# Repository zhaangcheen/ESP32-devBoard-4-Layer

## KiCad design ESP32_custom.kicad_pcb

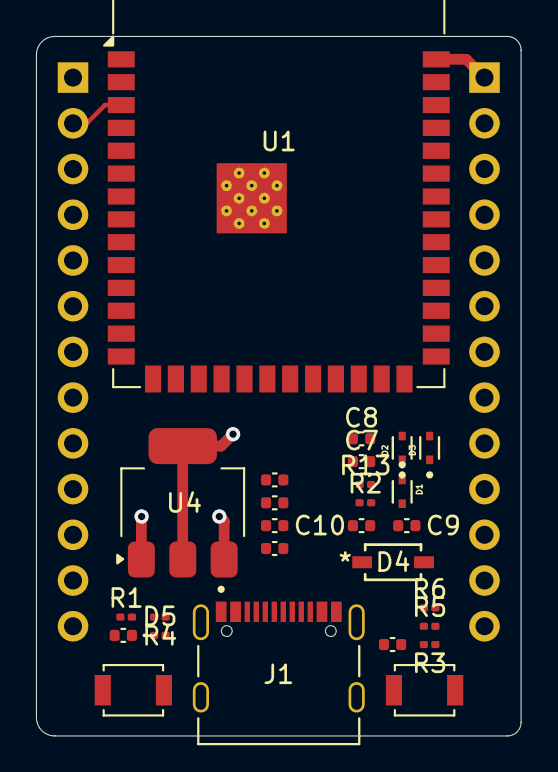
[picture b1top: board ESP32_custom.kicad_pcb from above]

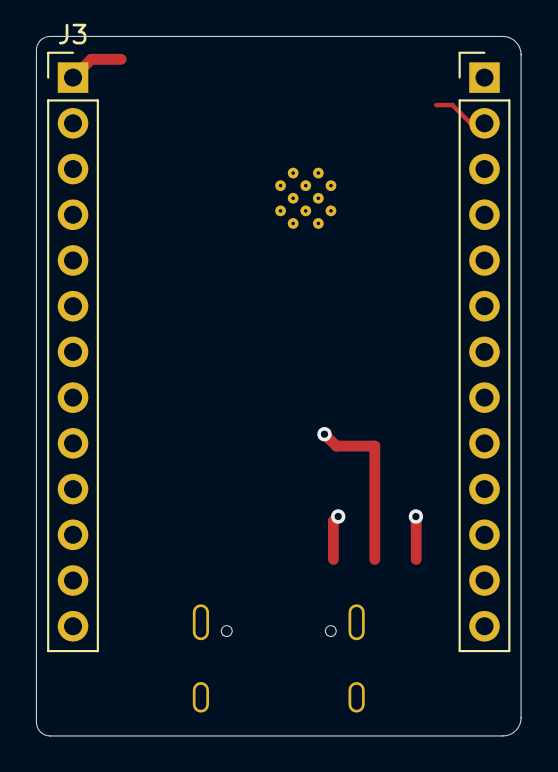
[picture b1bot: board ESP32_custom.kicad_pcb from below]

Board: 4 copper layers, 26.9 x 38.9 mm, 29 parts (2 on the bottom side), 14 nets.

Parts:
C1, C3, C5, C6, C7: 0u1F; C_0402_1005Metric
C2, C4, C8, C9: 10uF; C_0402_1005Metric
C10: 1uF; C_0402_1005Metric
D1, D2, D3: LESD5D5.0CT1G; TVS_LESD5D5.0CT1G
D4: 1N5819HW-7-F; 1N5819HW-7-F_DIO
D5: LED; LED_0201_0603Metric
J1: TYPE-C-31-M-12; HRO_TYPE-C-31-M-12
J2, J3: Conn_01x13_Pin; PinHeader_1x13_P2.54mm_Vertical
R1: 5.1K; R_0201_0603Metric
R2, R3, R13: 10K; R_0201_0603Metric
R4: 10k; R_0201_0603Metric
R5, R6: 5K1; R_0201_0603Metric
SW1, SW2: SW_Push; SW_SPST_B3U-1000P
U1: ESP32-S3-WROOM-1
U4: AMS1117-3.3; SOT-223-3_TabPin2

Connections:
+5V: C1.1, C2.1, C9.1, D4.2 (K), J2.13, U4.3 (VI)
/CHIP_PU: C6.1, C10.1, J2.2, R2.1, R4.2, SW2.1, U1.3 (EN)
/D+: D3.2, J1.A6 (DP1), J1.B6 (DP2), U1.14 (USB_D+)
/D-: D2.2, J1.A7 (DN1), J1.B7 (DN2), U1.13 (USB_D-)
/ESP_3V3: R2.2, R13.2, U1.2 (3V3)
/GPIO0: C5.1, R3.2, SW1.1, U1.27 (IO0)
/RX: J3.4, U1.36 (RXD0)
/TX: J3.5, U1.37 (TXD0)
GND: C1.2, C2.2, C3.2, C4.2, C5.2, C6.2, C7.2, C8.2, C9.2, C10.2, D1.1, D2.1, D3.1, D5.1 (K), J1.A1_B12 (GND), J1.B1_A12 (GND), J1.S1 (SHIELD), J1.S2 (SHIELD), J1.S3 (SHIELD), J1.S4 (SHIELD), J2.12, J3.1, R5.2, R6.2, SW1.2, SW2.2, U1.1 (GND), U1.40 (GND), U1.41 (GND), U4.1 (GND)
unnamed: D5.2 (A), R1.2
unnamed: J1.A5 (CC1), R6.1
unnamed: J1.B5 (CC2), R5.1
VBUS: D1.2, D4.1 (A), J1.A4_B9 (VBUS), J1.B4_A9 (VBUS)
VCC: C3.1, C4.1, C7.1, C8.1, J2.1, R1.1, R3.1, R4.1, R13.1, U4.2 (VO)
